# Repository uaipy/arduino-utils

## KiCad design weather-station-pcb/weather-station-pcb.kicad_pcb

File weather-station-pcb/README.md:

# Estação de Controle de Irrigação via LoRa

Bem-vindo ao repositório da placa de controle para um sistema de irrigação inteligente. Este projeto utiliza um microcontrolador ESP32 e comunicação sem fio de longo alcance LoRa para criar um "nó" de sensoriamento e acionamento que pode ser instalado diretamente no campo.

## 📜 Descrição

Esta PCB foi projetada para atuar como um nó remoto em um sistema de agricultura de precisão ou jardinagem automatizada. Ela não necessita de conexão com a internet (Wi-Fi), comunicando-se via rádio LoRa com uma estação base (gateway) que pode ser outro ESP32, um computador, ou uma unidade UAI.py conectada a uma porta serial. A placa serve como um hub para o módulo ESP32 (WIFI_KIT_32_V3), oferecendo conexões robustas para ler sensores de campo e acionar atuadores como válvulas ou bombas.

## ✨ Características Principais

* **Microcontrolador:** Soquete para o módulo ESP32 WIFI_KIT_32_V3.
* **Comunicação:** Conexões preparadas para um módulo de rádio LoRa, permitindo comunicação sem fio de longo alcance e baixo consumo de energia.
* **Conexões para Sensores e Atuadores:**
    * Bornes de parafuso (Screw Terminals) para conexões externas robustas com sensores (umidade do solo, nível de água, etc.) e atuadores (válvulas solenoide, relés).
    * Conectores dedicados para periféricos I2C (RTC, sensores de precisão) e SPI (cartão SD para data logging local).
* **Design Robusto para Campo:**
    * Plano de terra (Ground Plane) para maior estabilidade e imunidade a ruídos.
    * Furos de montagem para fixação em um case ou painel de controle.
    * Circuitos de desacoplamento e pull-up para garantir a integridade dos sinais dos sensores.

## 📁 Estrutura do Repositório

* **/hardware**: Contém todos os arquivos do projeto KiCad (esquemático, layout da PCB, etc.).
* **/firmware**: (Em desenvolvimento) Conterá o código-fonte para o ESP32, incluindo a lógica de controle e a comunicação via LoRa.
* **/gerber**: Arquivos Gerber e de furação prontos para enviar para uma fabricante de PCBs.
* **/docs**: Contém datasheets, logos e outros documentos de suporte.
* **/img**: Imagens e renders da placa.

## 🛠️ Fabricação

Para fabricar sua própria placa:
1.  Faça o download do arquivo `.zip` da pasta `/gerber`.
2.  Envie este arquivo para a sua fabricante de PCBs preferida (ex: JLCPCB, PCBWay, etc.).
3.  As configurações padrão (placa de 2 camadas, 1.6mm de espessura, cobre de 1oz) são suficientes.

## 📄 Licença

Este projeto é distribuído sob a licença MIT. Veja o arquivo `LICENSE` para mais detalhes.

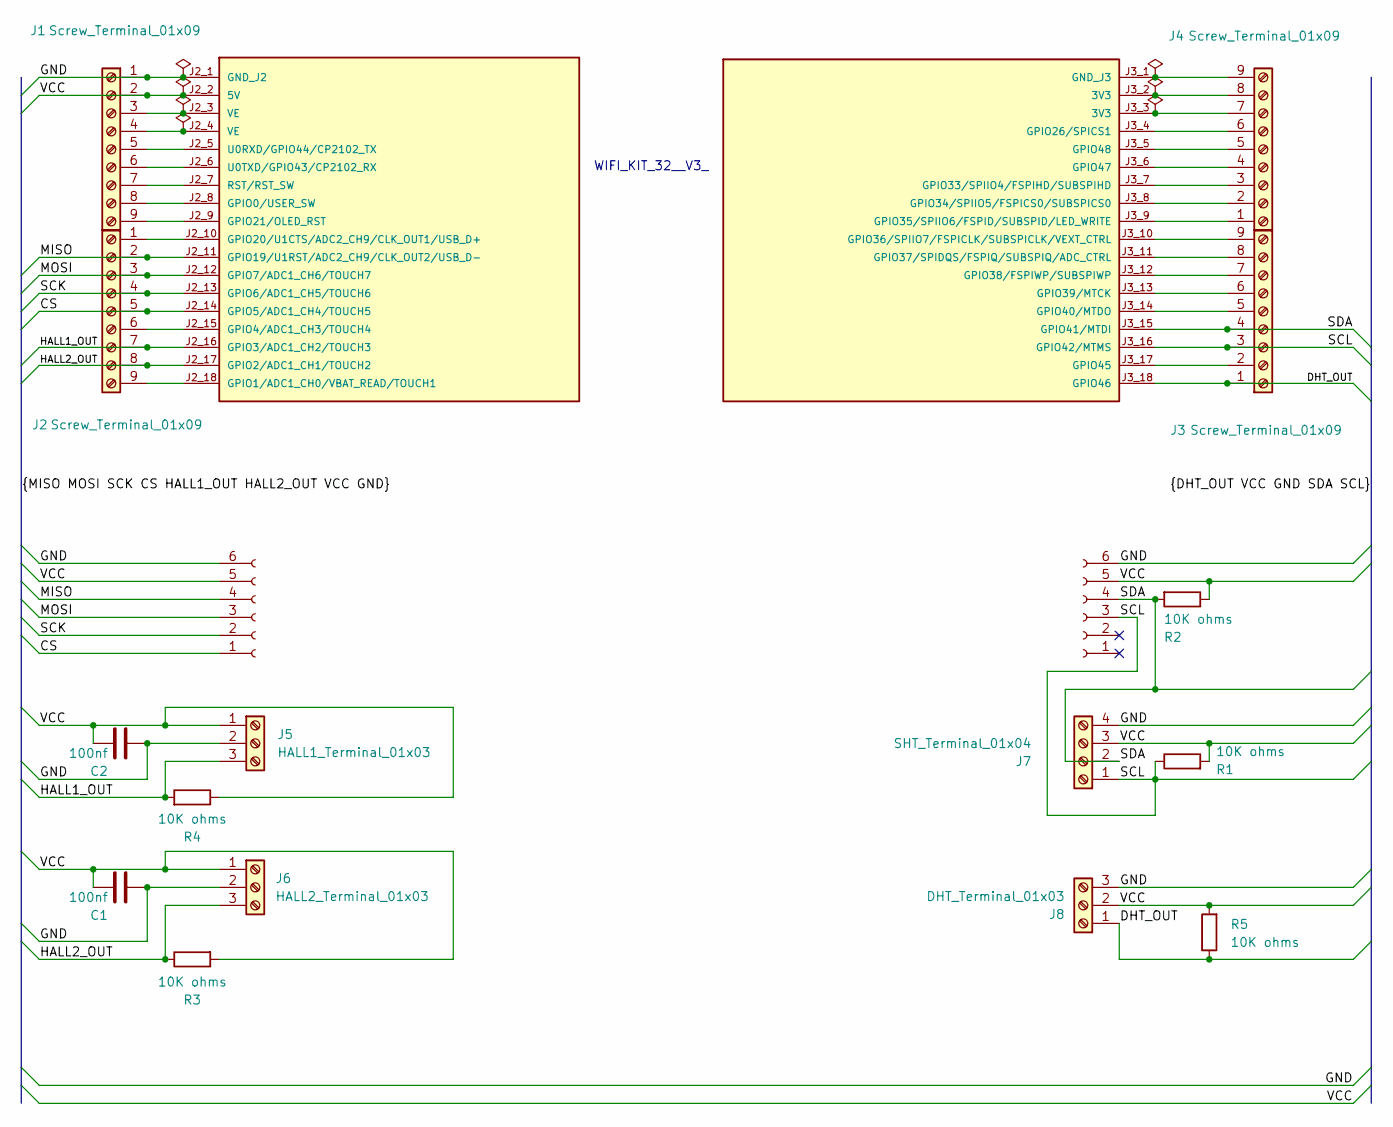
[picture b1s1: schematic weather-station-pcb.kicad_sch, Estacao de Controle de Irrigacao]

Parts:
C1, C2: 100nf; C_Disc_D3.0mm_W2.0mm_P2.50mm
J1, J2, J3, J4: Screw_Terminal_01x09; TerminalBlock_Phoenix_MKDS-1,5-9_1x09_P5.00mm_Horizontal
J5: HALL1_Terminal_01x03; TerminalBlock_Phoenix_MKDS-1,5-3_1x03_P5.00mm_Horizontal
J6: HALL2_Terminal_01x03; TerminalBlock_Phoenix_MKDS-1,5-3_1x03_P5.00mm_Horizontal
J7: SHT_Terminal_01x04; TerminalBlock_Phoenix_MKDS-1,5-4_1x04_P5.00mm_Horizontal
J8: DHT_Terminal_01x03; TerminalBlock_Phoenix_MKDS-1,5-3_1x03_P5.00mm_Horizontal
J9: Conn_01x06_Socket; PinSocket_1x06_P1.00mm_Vertical
J10: Conn_01x06_Socket; PinSocket_1x06_P1.00mm_Vertical_v2
R1, R2, R3, R4, R5: 10K ohms; R_Axial_DIN0207_L6.3mm_D2.5mm_P10.16mm_Horizontal
U1: WIFI_KIT_32__V3_; MODULE_WIFI_KIT_32__V3_; PARTREV Rev 1.1

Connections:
/CS: J2.5, J9.1, U1.J2_14 (GPIO5/ADC1_CH4/TOUCH5)
/DHT_OUT: J3.1, J8.1, R5.1, U1.J3_18 (GPIO46)
/GND: C1.2, C2.1, J1.1, J5.2, J6.2, J7.4, J8.3, J9.6, J10.6, U1.J2_1 (GND_J2)
/HALL1_OUT: J2.7, J5.3, R4.2, U1.J2_16 (GPIO3/ADC1_CH2/TOUCH3)
/HALL2_OUT: J2.8, J6.3, R3.1, U1.J2_17 (GPIO2/ADC1_CH1/TOUCH2)
/MISO: J2.2, J9.4, U1.J2_11 (GPIO19/U1RST/ADC2_CH9/CLK_OUT2/USB_D-)
/MOSI: J2.3, J9.3, U1.J2_12 (GPIO7/ADC1_CH6/TOUCH7)
/SCK: J2.4, J9.2, U1.J2_13 (GPIO6/ADC1_CH5/TOUCH6)
/SCL: J3.3, J7.1, J10.3, R1.1, U1.J3_16 (GPIO42/MTMS)
/SDA: J3.4, J7.2, J10.4, R2.2, U1.J3_15 (GPIO41/MTDI)
/VCC: C1.1, C2.2, J1.2, J5.1, J6.1, J7.3, J8.2, J9.5, J10.5, R1.2, R2.1, R3.2, R4.1, R5.2, U1.J2_2 (5V)
unnamed: J1.3, U1.J2_3 (VE)
unnamed: J1.4, U1.J2_4 (VE)
unnamed: J1.5, U1.J2_5 (U0RXD/GPIO44/CP2102_TX)
unnamed: J1.6, U1.J2_6 (U0TXD/GPIO43/CP2102_RX)
unnamed: J1.7, U1.J2_7 (RST/RST_SW)
unnamed: J1.8, U1.J2_8 (GPIO0/USER_SW)
unnamed: J1.9, U1.J2_9 (GPIO21/OLED_RST)
unnamed: J2.1, U1.J2_10 (GPIO20/U1CTS/ADC2_CH9/CLK_OUT1/USB_D+)
unnamed: J2.6, U1.J2_15 (GPIO4/ADC1_CH3/TOUCH4)
unnamed: J2.9, U1.J2_18 (GPIO1/ADC1_CH0/VBAT_READ/TOUCH1)
unnamed: J3.2, U1.J3_17 (GPIO45)
unnamed: J3.5, U1.J3_14 (GPIO40/MTDO)
unnamed: J3.6, U1.J3_13 (GPIO39/MTCK)
unnamed: J3.7, U1.J3_12 (GPIO38/FSPIWP/SUBSPIWP)
unnamed: J3.8, U1.J3_11 (GPIO37/SPIDQS/FSPIQ/SUBSPIQ/ADC_CTRL)
unnamed: J3.9, U1.J3_10 (GPIO36/SPIIO7/FSPICLK/SUBSPICLK/VEXT_CT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)
unnamed: J4.1, U1.J3_9 (GPIO35/SPIIO6/FSPID/SUBSPID/LED_WRITE)
unnamed: J4.2, U1.J3_8 (GPIO34/SPIIO5/FSPICS0/SUBSPICS0)
unnamed: J4.3, U1.J3_7 (GPIO33/SPIIO4/FSPIHD/SUBSPIHD)
unnamed: J4.4, U1.J3_6 (GPIO47)
unnamed: J4.5, U1.J3_5 (GPIO48)
unnamed: J4.6, U1.J3_4 (GPIO26/SPICS1)
unnamed: J4.7, U1.J3_3 (3V3)
unnamed: J4.8, U1.J3_2 (3V3)
unnamed: J4.9, U1.J3_1 (GND_J3)

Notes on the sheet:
WIFI_KIT_32__V3_

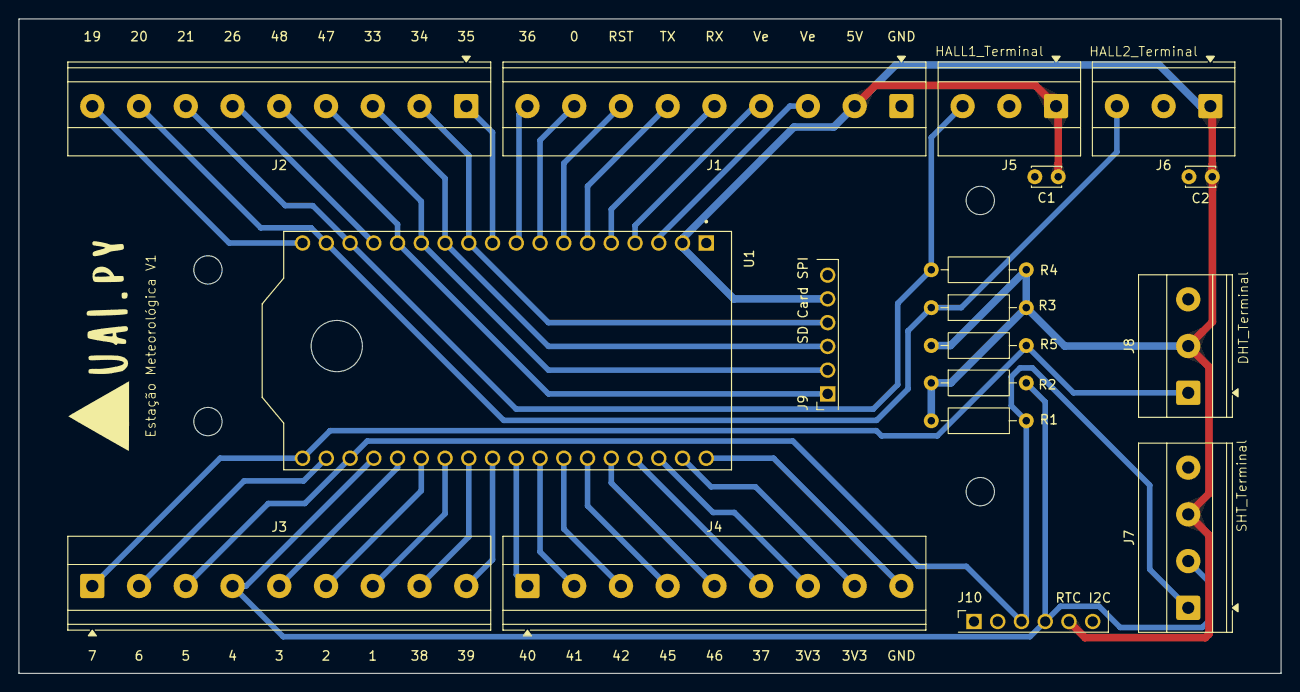
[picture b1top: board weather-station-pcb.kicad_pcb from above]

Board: 2 copper layers, 135.0 x 70.0 mm, 18 parts (0 on the bottom side), 36 nets.

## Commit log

2023-08-19 feat: read arduino by serial port
2023-08-19 chore: add axios dependencie
2023-08-19 feat: create proxy request
2023-08-19 fix: add localhost connection
2023-08-27 feat: add message read date
2023-08-29 feat: add arduino code
2024-07-03 feat: add esp8266 code
2025-04-12 feat: adiciona envio de temperatura via MQTT usando ESP8266
2025-04-18 feat: add temperature sending via MQTT using ESP8266
2025-04-19 feat: update MQTT logic in esp/mqtt-poc.ino
2025-06-02 feat(lora): add sender, receiver and rtc_config components
2025-06-03 fix: prevent buffer overflow on LoRa packet reception
2025-07-12 feat: support rain detection via ISR and SD data logging
2025-07-18 feat: move js serial reader
2025-07-19 feat: add python serial reader
2025-07-19 feat: update requests
2025-07-19 feat: add loop to handle errors
2025-07-19 feat: update endpoint
2025-07-19 feat: update main
2025-10-11 feat: add pcb design
